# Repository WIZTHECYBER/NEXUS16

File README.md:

### **Nexus16: The Art of Control.**

>A 17-year-old and a 16-year-old, ordinary people in this world just trying to learn the ways of the world and finding our interests. Well, we found our way through Hack Club.
>They became the platform for us to start our skill development from the start and provided us with a challenging yet sufficient project to physically work on.
>A lot of the DIY projects are mostly individual hardware soldered together to form a working but fragile piece of machinery, but to us that was not going to cut it. So we decided to use professional approaches and slowly but surely we were making progress, and finally, now our hard work has paid off.

### **Meet the Nexus16:**
>Designed from the ground up to give you pure, uninterrupted control over your work, built to make you a professional and to provide you with a satisfactory experience.

### **The Engineering behind the PCB:**
>We made sure to input the details of Nexus16 in such a sophisticated manner that it is easy for everyone to learn, self-develop, and improvise it.

### **Casing:**
>We did not settle for an exquisite and overly-engineered design but rather chose to make the casing simple enough to 3D print for even low-tier 3D printers. Well, after spending a few grueling hours understanding and learning AutoCAD, we fabricated a design that looked simple and sturdy enough for our demands. The microcontroller and OLED sit safely on a raised platform, while the 16 mechanical switches drop perfectly into 3.5mm hollow "tubs". This provides the user with an angle on the hands that is not concerning in the long run.

### **Digital Dashboard:**
> To provide an improved experience, we also included an OLED Display for visual output. The seamlessly integrated 0.91" OLED screen acts as the system status, visible at a single glance.

### **Pure, Tactile Experience:**
> No fancy or magnetic switches were decided to be used to provide the builders of this project with simple and cost-effective yet sustainable components. Just 16 highly responsive mechanical switches (MX Cherry) were perfect for our demands.

### **Bill of Materials (BOM):**
>To manufacture your own Nexus16, you will need:

>1x Seeed Studio XIAO RP2040

>1x 0.91" I2C OLED Display

>16x MX-Style Mechanical Switches

>16x Premium Keycaps

>1x Custom Nexus16 PCB

>16x Mini-E-LEDs

>1x 3D Printed Top Case & Bottom Case (Files located in the Production folder)

### **Building Guide:**
>We have open-sourced our entire project so you can build it all by yourselves.

>All files are organized, ready to be downloaded, to be inserted into software, and to be fabricated:
The Case: Grab the .STEP files from the Production folder and load them into your 3D printer. Our two-piece design prints flawlessly without the need for excessive print supports.

### **The PCB:**
>Send the gerbers.zip in the Production folder to your favorite PCB manufacturer.

### **How to Flash the Firmware:**
>Unplug the macropad from your computer.

>Press and hold the BOOTSEL button on the XIAO RP2040.

>While holding the button down, plug the USB cable into your computer.

>Release the BOOTSEL button. A new USB drive (usually called RPI-RP2) will pop up on your computer. This means it is in bootloader mode.

>Drag and drop your compiled .uf2 firmware file directly into that USB drive.

>The RP2040 will automatically disconnect, reboot, and start running your macropad code!
>The Brain: Flash the board in seconds using the files provided in the Firmware folder.

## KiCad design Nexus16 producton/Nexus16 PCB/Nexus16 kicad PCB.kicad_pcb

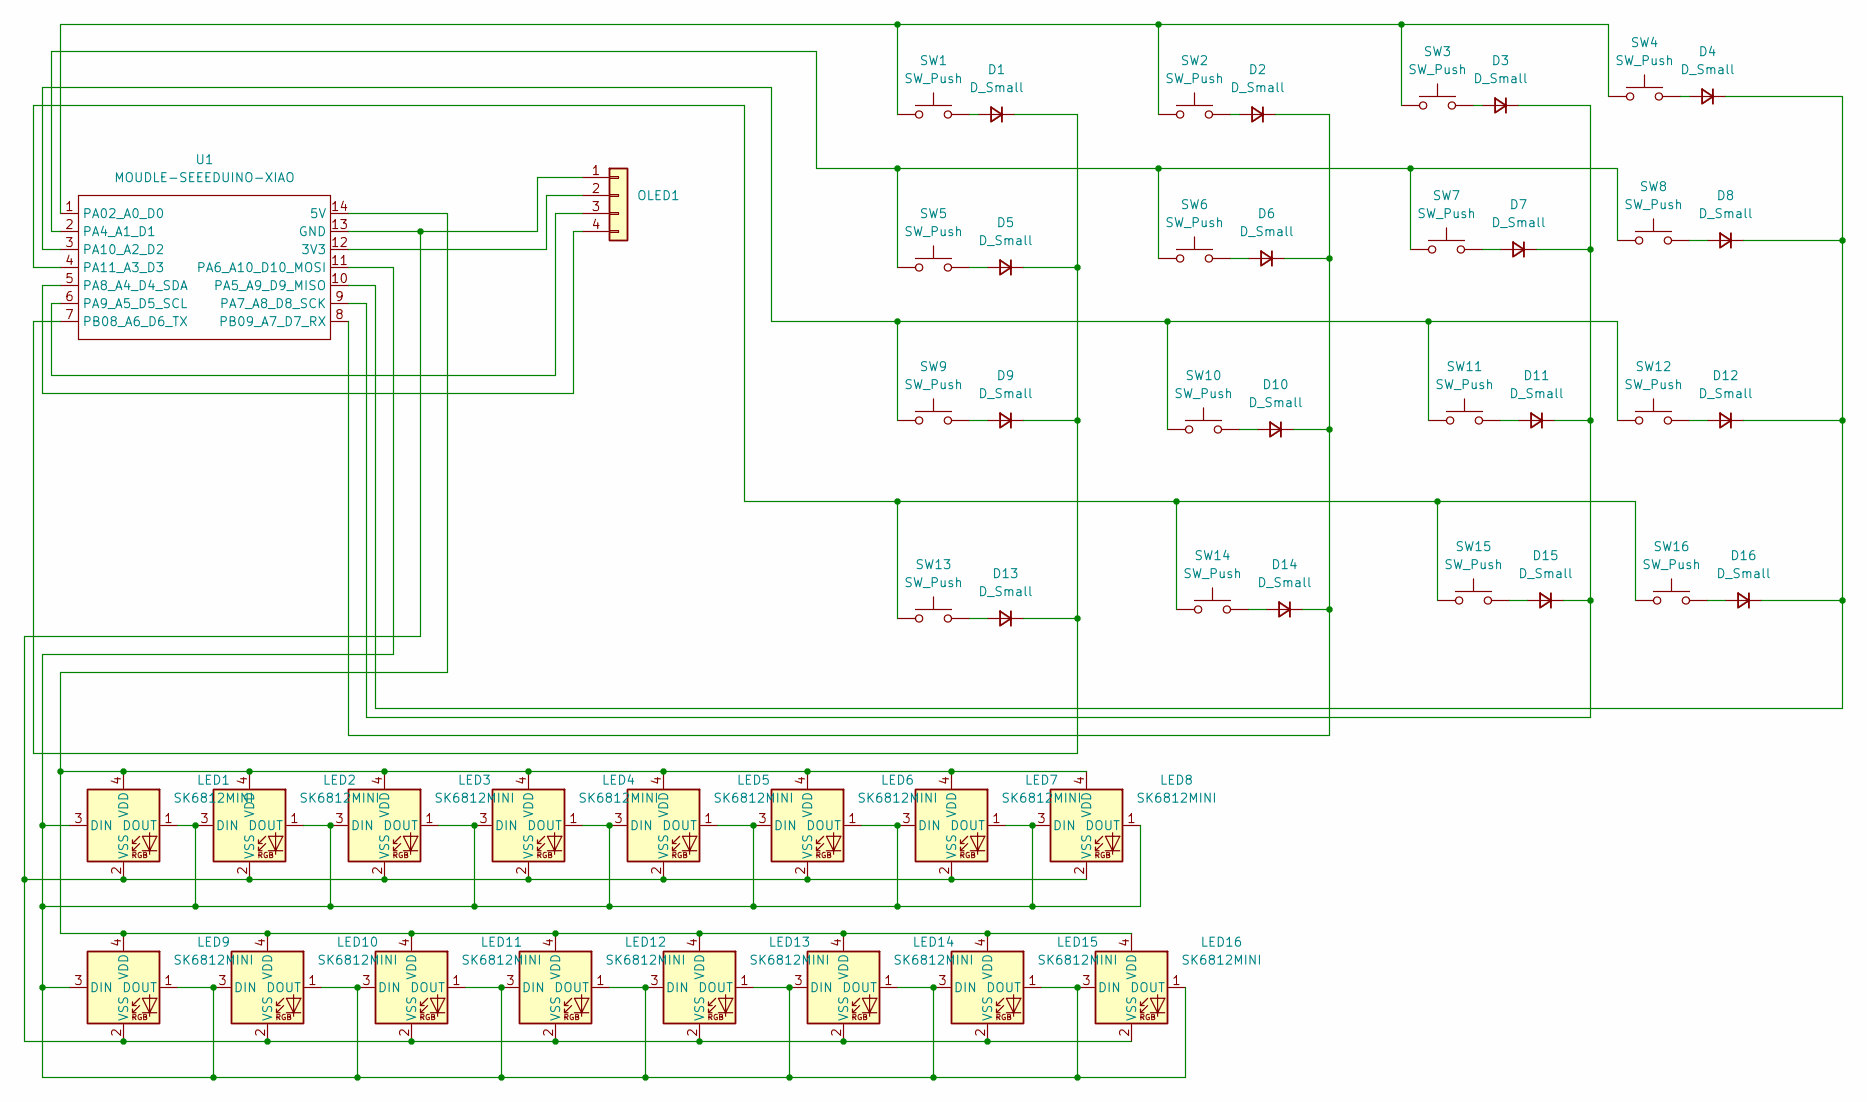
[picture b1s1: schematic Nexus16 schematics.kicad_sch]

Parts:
D1, D2, D3, D4, D5, D6, D7, D8, D9, D10, D11, D12, D13, D14, D15, D16: D_Small; D_DO-35_SOD27_P7.62mm_Horizontal
LED1, LED2, LED3, LED4, LED5, LED6, LED7, LED8, LED9, LED10, LED11, LED12, LED13, LED14, LED15, LED16: SK6812MINI; SK6812MINI-E_fixed
OLED1: PinSocket_1x04_P2.54mm_Vertical
SW1, SW2, SW3, SW4, SW5, SW6, SW7, SW8, SW9, SW10, SW11, SW12, SW13, SW14, SW15, SW16: SW_Push; SW_Cherry_MX_1.00u_PCB
U1: MOUDLE-SEEEDUINO-XIAO; XIAO-Generic-Hybrid-14P-2.54-21X17.8MM

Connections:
unnamed: D1.2 (A), SW1.2
unnamed: D1.1 (K), D5.1 (K), D9.1 (K), D13.1 (K), U1.7 (PB08_A6_D6_TX)
unnamed: D2.2 (A), SW2.2
unnamed: D3.2 (A), SW3.2
unnamed: D4.2 (A), SW4.2
unnamed: D5.2 (A), SW5.2
unnamed: D6.2 (A), SW6.2
unnamed: D7.2 (A), SW7.2
unnamed: D8.2 (A), SW8.2
unnamed: D9.2 (A), SW9.2
unnamed: D10.2 (A), SW10.2
unnamed: D2.1 (K), D6.1 (K), D10.1 (K), D14.1 (K), U1.8 (PB09_A7_D7_RX)
unnamed: D11.2 (A), SW11.2
unnamed: D3.1 (K), D7.1 (K), D11.1 (K), D15.1 (K), U1.9 (PA7_A8_D8_SCK)
unnamed: D12.2 (A), SW12.2
unnamed: D4.1 (K), D8.1 (K), D12.1 (K), D16.1 (K), U1.10 (PA5_A9_D9_MISO)
unnamed: D13.2 (A), SW13.2
unnamed: D14.2 (A), SW14.2
unnamed: D15.2 (A), SW15.2
unnamed: D16.2 (A), SW16.2
unnamed: LED1.1 (DOUT), LED1.3 (DIN), LED2.1 (DOUT), LED2.3 (DIN), LED3.1 (DOUT), LED3.3 (DIN), LED4.1 (DOUT), LED4.3 (DIN), LED5.1 (DOUT), LED5.3 (DIN), LED6.1 (DOUT), LED6.3 (DIN), LED7.1 (DOUT), LED7.3 (DIN), LED8.1 (DOUT), LED8.3 (DIN), LED9.1 (DOUT), LED9.3 (DIN), LED10.1 (DOUT), LED10.3 (DIN), LED11.1 (DOUT), LED11.3 (DIN), LED12.1 (DOUT), LED12.3 (DIN), LED13.1 (DOUT), LED13.3 (DIN), LED14.1 (DOUT), LED14.3 (DIN), LED15.1 (DOUT), LED15.3 (DIN), LED16.1 (DOUT), LED16.3 (DIN), U1.11 (PA6_A10_D10_MOSI)
unnamed: LED1.4 (VDD), LED2.4 (VDD), LED3.4 (VDD), LED4.4 (VDD), LED5.4 (VDD), LED6.4 (VDD), LED7.4 (VDD), LED8.4 (VDD), LED9.4 (VDD), LED10.4 (VDD), LED11.4 (VDD), LED12.4 (VDD), LED13.4 (VDD), LED14.4 (VDD), LED15.4 (VDD), LED16.4 (VDD), U1.14 (5V)
unnamed: LED1.2 (VSS), LED2.2 (VSS), LED3.2 (VSS), LED4.2 (VSS), LED5.2 (VSS), LED6.2 (VSS), LED7.2 (VSS), LED8.2 (VSS), LED9.2 (VSS), LED10.2 (VSS), LED11.2 (VSS), LED12.2 (VSS), LED13.2 (VSS), LED14.2 (VSS), LED15.2 (VSS), LED16.2 (VSS), OLED1.1, U1.13 (GND)
unnamed: OLED1.2, U1.12 (3V3)
unnamed: OLED1.3, U1.6 (PA9_A5_D5_SCL)
unnamed: OLED1.4, U1.5 (PA8_A4_D4_SDA)
unnamed: SW1.1, SW2.1, SW3.1, SW4.1, U1.1 (PA02_A0_D0)
unnamed: SW5.1, SW6.1, SW7.1, SW8.1, U1.2 (PA4_A1_D1)
unnamed: SW9.1, SW10.1, SW11.1, SW12.1, U1.3 (PA10_A2_D2)
unnamed: SW13.1, SW14.1, SW15.1, SW16.1, U1.4 (PA11_A3_D3)

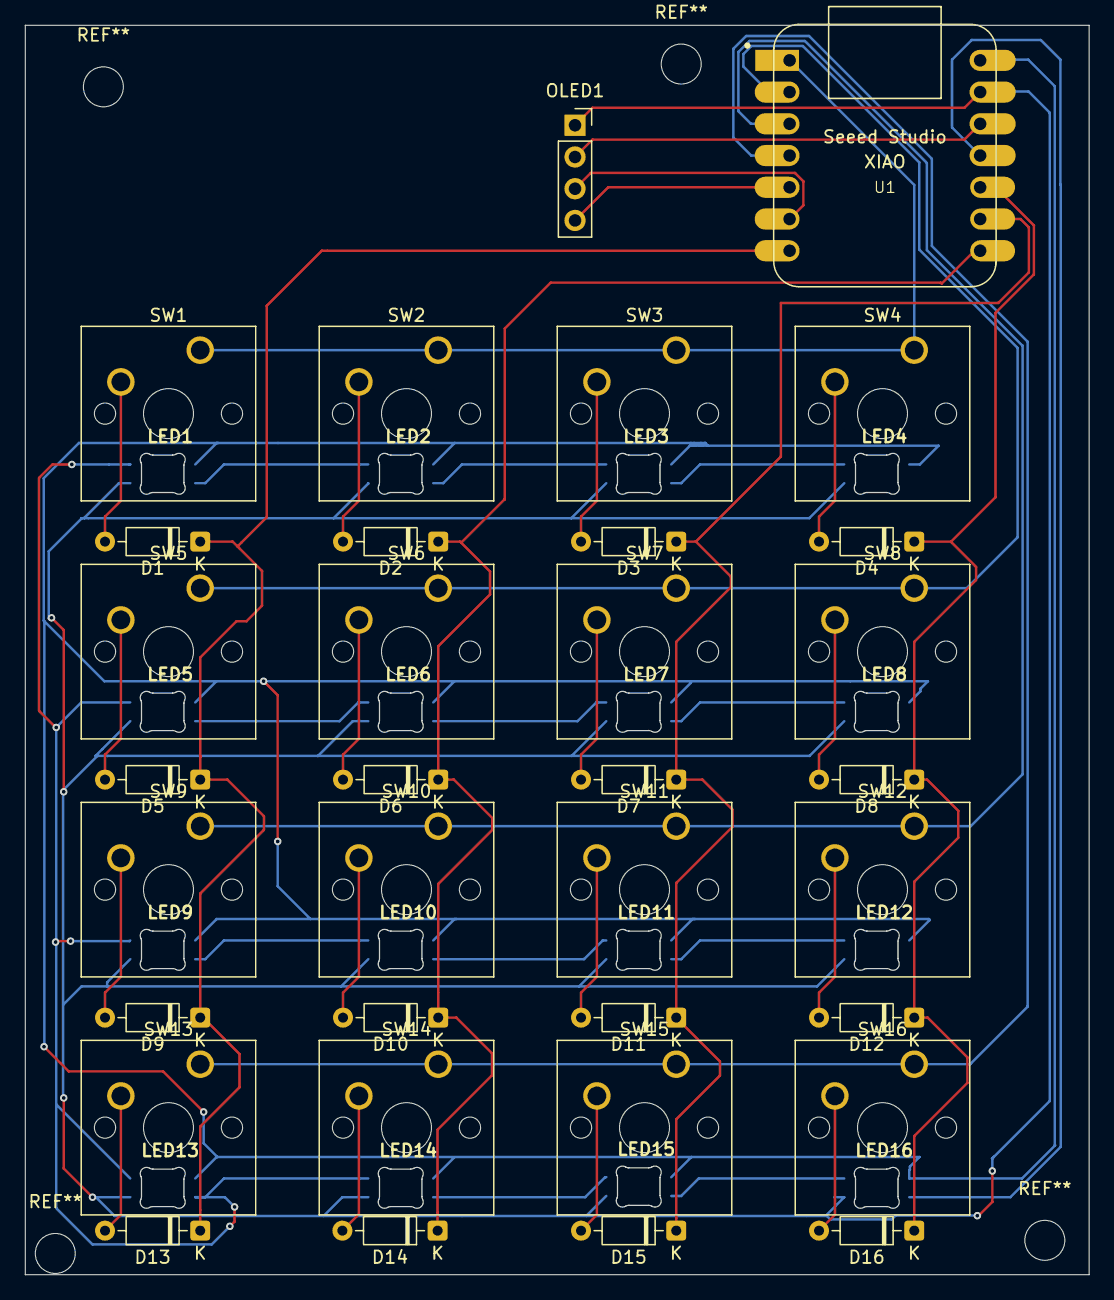
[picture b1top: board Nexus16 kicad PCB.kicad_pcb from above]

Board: 2 copper layers, 85.2 x 100.0 mm, 50 parts (0 on the bottom side), 30 nets.

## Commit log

2026-03-21 Create Firmware
2026-03-21 Create Nexus16 Firmware
